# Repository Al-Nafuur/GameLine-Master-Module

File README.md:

# GameLine-Master-Module
Reverse engineered schematics and firmware of the CVC GameLine Master Module

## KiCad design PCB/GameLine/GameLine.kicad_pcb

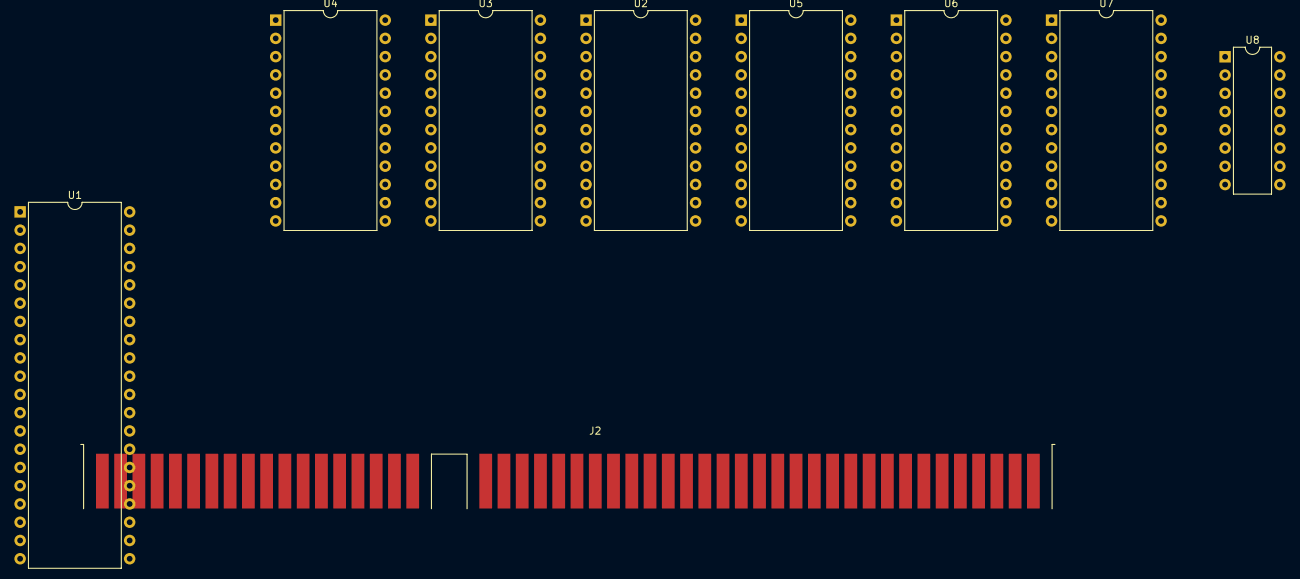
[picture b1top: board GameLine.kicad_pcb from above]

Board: 2 copper layers, 9 parts (0 on the bottom side), 5 nets, no tracks yet.

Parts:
J2: Conn_02x12_Counter_Clockwise; BUS_AT
U1: 266777A-HCS_10018-8319_7F; DIP-40_W15.24mm
U2: RCA CDM6116E2; DIP-24_W15.24mm
U3, U4, U5, U6: MB8416-20; DIP-24_W15.24mm
U7: CVC-A1065; DIP-24_W15.24mm
U8: DM54S288J; DIP-16_W7.62mm

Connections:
+5V: J2.23, U1.40 (VCC), U2.24 (VCC), U3.24 (VCC), U4.24 (VCC), U5.24 (VCC), U6.24 (VCC), U7.24 (VCC), U8.16 (VCC)
GND: J2.12, J2.24, U1.1 (VSS), U1.20 (VSS), U2.12 (GND), U3.12 (GND), U4.12 (GND), U5.12 (GND), U6.12 (GND), U7.12 (GND), U8.8 (GND)
unnamed: U1.22 (RAM_A10), U2.19 (A10), U3.19 (A10), U4.19 (A10), U5.19 (A10), U6.19 (A10), U7.19 (A10)
unnamed: U1.26 (RAM_WE), U3.21 (~WE), U4.21 (~WE), U5.21 (~WE), U6.21 (~WE)
unnamed: U1.29 (ROM_A11?), U7.21 (A11?)

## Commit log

2023-05-16 More Images
2023-05-16 initial disassembly
2023-05-16 latest update from new dump
2023-05-16 added fixed ROM dump
2023-05-18 some small progress
2023-05-18 merged source codes
2023-05-18 renamed GL-registers
2023-05-23 bessere Kommentierung des Ladens
2023-05-24 some minor improvements
2023-05-25 improved understanding of draw routines
2023-05-27 reordered banks adjusted bankswitching constants added some Kevtris findings exchanged ROM
2023-09-22 added fixed dump and code
